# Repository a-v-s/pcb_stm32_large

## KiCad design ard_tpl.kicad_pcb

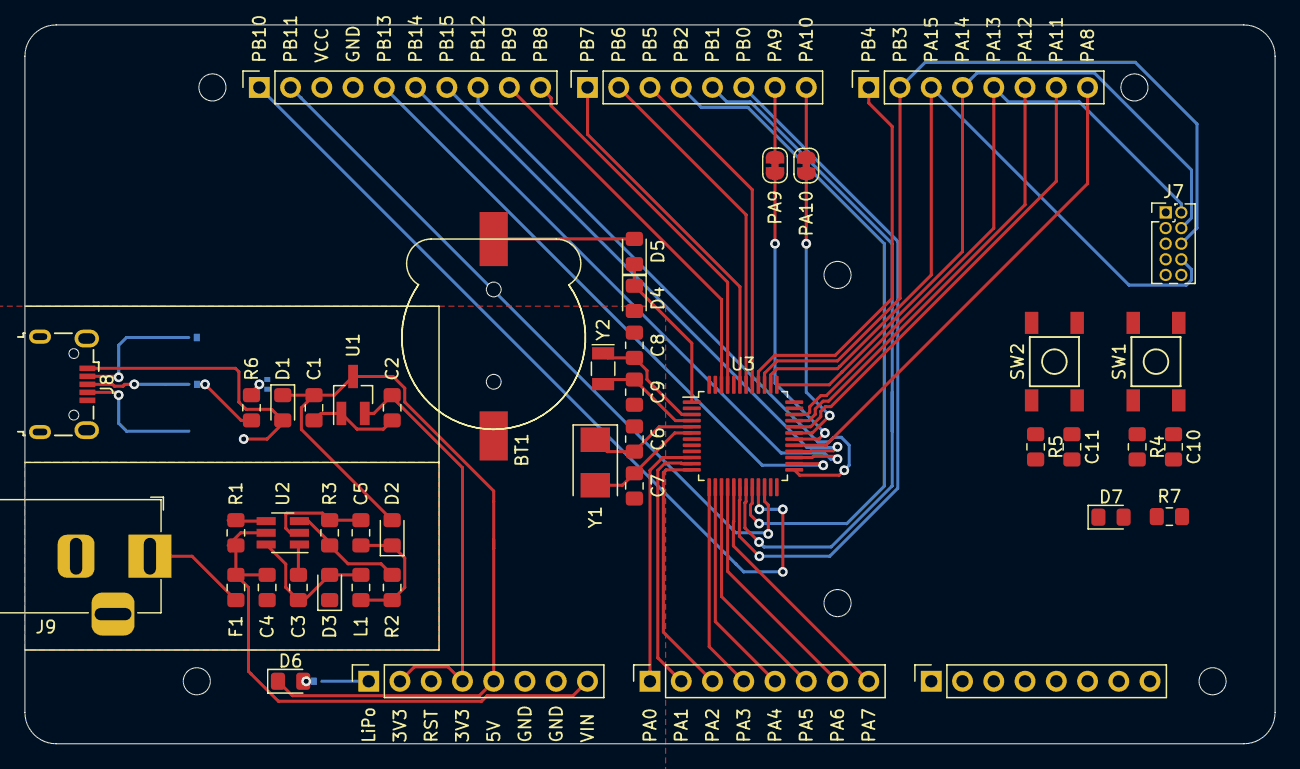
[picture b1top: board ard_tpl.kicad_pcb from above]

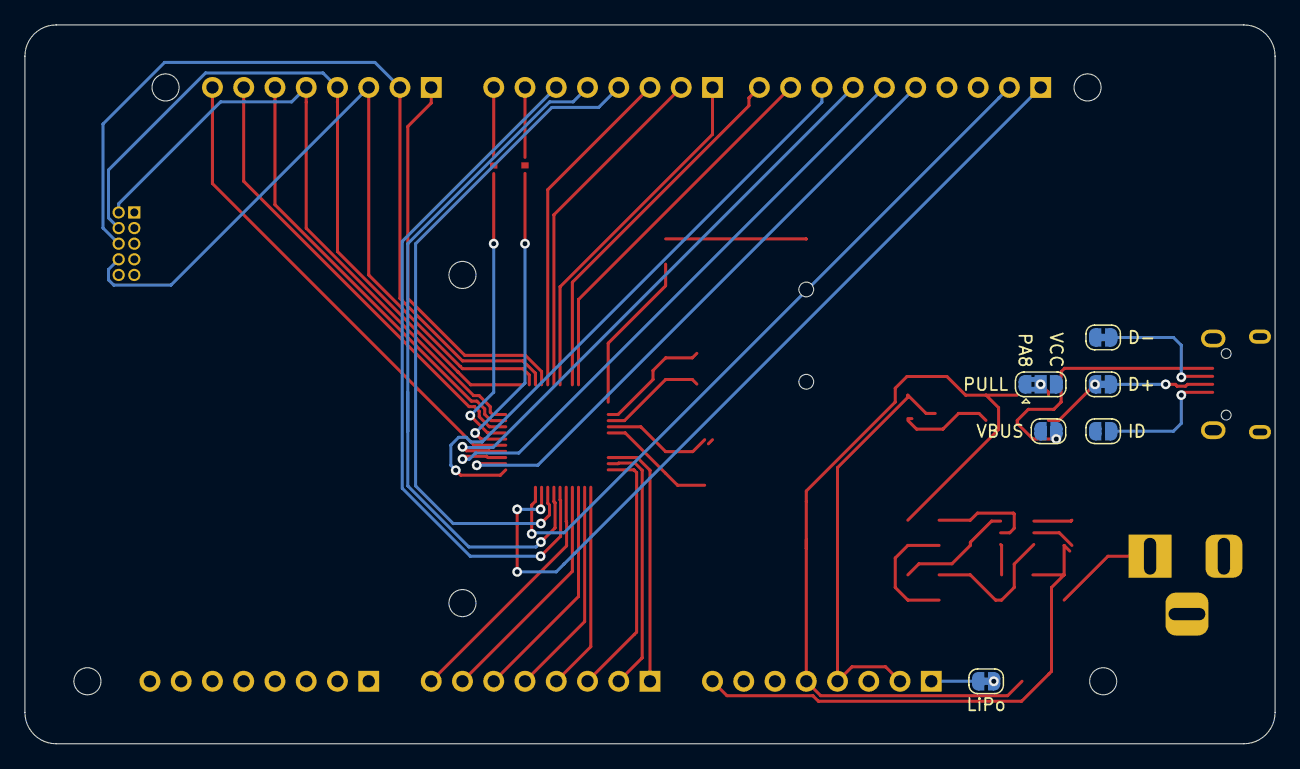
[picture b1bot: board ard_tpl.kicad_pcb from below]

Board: 2 copper layers, 101.6 x 58.4 mm, 58 parts (6 on the bottom side), 62 nets.

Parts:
BT1: Battery_Cell; QJ1220-2SMT
C1, C2: 1u; C_0805_2012Metric_Pad1.15x1.40mm_HandSolder
C3: C_Small; C_0805_2012Metric_Pad1.15x1.40mm_HandSolder
C4, C5: 10uF; C_0805_2012Metric_Pad1.15x1.40mm_HandSolder
C6, C7: 30 pF; C_0805_2012Metric_Pad1.15x1.40mm_HandSolder
C8, C9: 10 pF; C_0805_2012Metric_Pad1.15x1.40mm_HandSolder
C10, C11: 100nF; C_0805_2012Metric_Pad1.15x1.40mm_HandSolder
D1, D2, D3, D4, D5, D6: D_Schottky; D_0805_2012Metric_Pad1.15x1.40mm_HandSolder
D7: LED_Small; LED_0805_2012Metric_Pad1.15x1.40mm_HandSolder
F1: Polyfuse_Small; Fuse_0805_2012Metric_Pad1.15x1.40mm_HandSolder
H1, H2, H3, H4, H5, H6: MountingHole; MountingHole_2.2mm_M2
J1, J3, J4, J5, J6: Conn_01x08; PinSocket_1x08_P2.54mm_Vertical
J2: Conn_01x10; PinSocket_1x10_P2.54mm_Vertical
J7: Conn_02x05_Odd_Even; PinHeader_2x05_P1.27mm_Vertical
J8: USB_B_Micro; USB_Micro-B_Wuerth_629105150521
J9: Jack-DC; BarrelJack_Horizontal
JP1: D+; SolderJumper-2_P1.3mm_Bridged_RoundedPad1.0x1.5mm
JP2: D-; SolderJumper-2_P1.3mm_Bridged_RoundedPad1.0x1.5mm
JP3: ID; SolderJumper-2_P1.3mm_Open_RoundedPad1.0x1.5mm
JP4: LiPo; SolderJumper-2_P1.3mm_Bridged_RoundedPad1.0x1.5mm
JP5: VBUS; SolderJumper-2_P1.3mm_Open_RoundedPad1.0x1.5mm
JP6: PA9; SolderJumper-2_P1.3mm_Bridged_RoundedPad1.0x1.5mm
JP7: PA10; SolderJumper-2_P1.3mm_Bridged_RoundedPad1.0x1.5mm
JP8: PULL; SolderJumper-3_P1.3mm_Bridged2Bar12_RoundedPad1.0x1.5mm
L1: L_Small; L_0805_2012Metric_Pad1.15x1.40mm_HandSolder
R1, R3, R4, R5: 10K; R_0805_2012Metric_Pad1.15x1.40mm_HandSolder
R2: R_Small; R_0805_2012Metric_Pad1.15x1.40mm_HandSolder
R6, R7: 1K5; R_0805_2012Metric_Pad1.15x1.40mm_HandSolder
SW1, SW2: SW_Push; TS-1187
U1: MCP1700-3302E_SOT23; SOT-23_Handsoldering
U2: LMR16006YQ; SOT-23-6_Handsoldering
U3: STM32F103C8Tx; LQFP-48_7x7mm_P0.5mm
Y1: 8MHz, 20pF; Crystal_SMD_5032-2Pin_5.0x3.2mm
Y2: 32.768KHz 7pF; Crystal_SMD_EuroQuartz_EQ161-2Pin_3.2x1.5mm

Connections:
+3V8: J1.1, JP4.1
+5V: C1.1, D1.1, D2.2, D6.1, J1.5, U1.3
+12V: C4.1, F1.1, J1.8, R1.1, U2.5
+BATT: D4.1, D5.1, U3.1
BOOT0: C11.2, R5.2, SW2.1, U3.44
GND: BT1.2, C1.2, C2.2, C4.2, C5.2, C6.2, C7.2, C8.2, C9.2, C10.1, D3.1, J1.6, J1.7, J2.4, J7.3, J7.7, J7.9, J8.5, J8.6, J9.2, R3.2, R5.1, SW1.2, U1.1, U2.2, U3.8, U3.23, U3.35, U3.47
JTCK: J6.4, J7.4, U3.37
JTDI: J6.3, J7.8, U3.38
JTDO: J6.2, J7.6, U3.39
JTMS: J6.5, J7.2, U3.34
JnTRST: J6.1, U3.40
unnamed: BT1.1, D5.2
unnamed: C3.1, D3.2, L1.1, U2.6
unnamed: C3.2, U2.1
unnamed: C5.1, D2.1, L1.2, R2.2
unnamed: D1.2, J8.1, JP5.1
unnamed: D6.2, JP4.2
unnamed: D7.2, R7.2
unnamed: F1.2, J9.1
unnamed: J4.7, JP6.2
unnamed: J4.8, JP7.2
unnamed: J8.2, JP2.1
unnamed: J8.3, JP1.1
unnamed: J8.4, JP3.1
unnamed: JP8.2, R6.2
unnamed: R1.2, U2.4
unnamed: R2.1, R3.1, U2.3
PA0: J3.1, U3.10
PA1: J3.2, U3.11
PA2: J3.3, U3.12
PA3: J3.4, U3.13
PA4: J3.5, U3.14
PA5: J3.6, U3.15
PA6: J3.7, U3.16
PA7: J3.8, U3.17
PA8: J6.8, JP8.1, U3.29
PA9: JP5.2, JP6.1, U3.30
PA10: JP3.2, JP7.1, U3.31
PA11: J6.7, JP2.2, U3.32
PA12: J6.6, JP1.2, R6.1, U3.33
PB0: J4.6, U3.18
PB1: J4.5, U3.19
PB2: J4.4, U3.20
PB5: J4.3, U3.41
PB6: J4.2, U3.42
PB7: J4.1, U3.43
PB8: J2.10, U3.45
PB9: J2.9, U3.46
PB10: J2.1, U3.21
PB11: J2.2, U3.22
PB12: J2.8, U3.25
PB13: J2.5, U3.26
PB14: J2.6, U3.27
PB15: J2.7, U3.28
PC13: D7.1, U3.2
VCC: C2.1, C11.1, D4.2, J1.2, J1.4, J2.3, J7.1, JP8.3, R4.1, R7.1, SW2.2, U1.2, U3.9, U3.24, U3.36, U3.48
X8M1: C6.1, U3.5, Y1.1
X8M2: C7.1, U3.6, Y1.2
X32K1: C8.1, U3.3, Y2.1
X32K2: C9.1, U3.4, Y2.2
nRST: C10.2, J1.3, R4.2, SW1.1
nSRST: J7.10, U3.7

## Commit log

2020-05-21 Reannotate
2020-05-21 stm32
2020-05-21 Defining USB and JTAG pins
2020-05-21 rtc battery
2020-05-23 Partitially routed
2020-05-25 Adding a fuse
